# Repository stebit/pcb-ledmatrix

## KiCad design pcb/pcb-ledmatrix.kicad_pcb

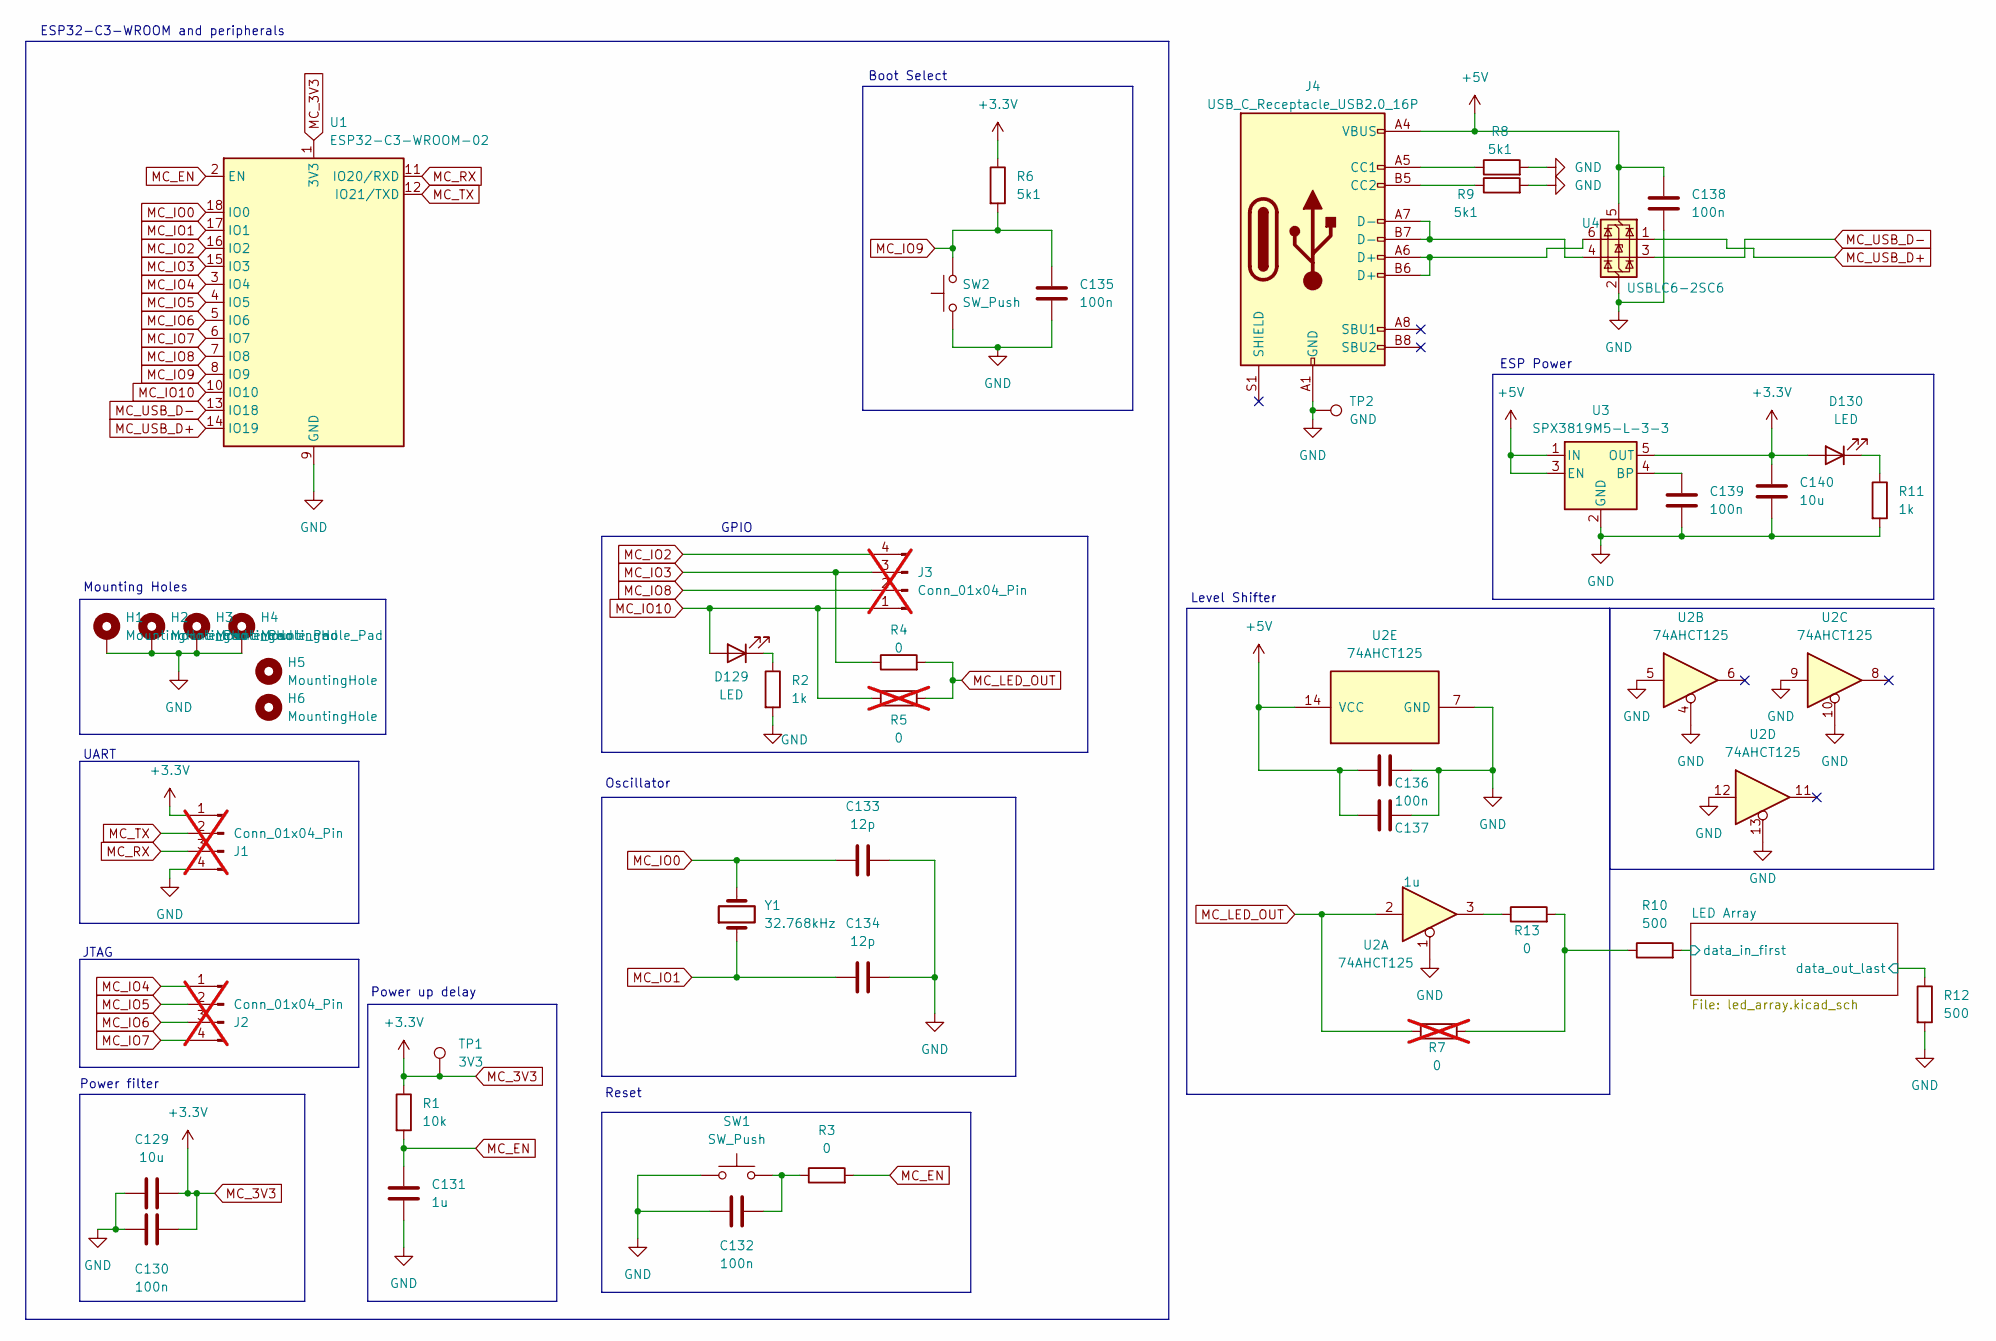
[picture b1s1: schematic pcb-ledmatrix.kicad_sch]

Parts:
C129, C140: 10u; C_0603_1608Metric
C130, C132, C135, C136, C138, C139: 100n; C_0603_1608Metric
C131, C137: 1u; C_0603_1608Metric
C133, C134: 12p; C_0603_1608Metric
D129, D130: LED; LED_0603_1608Metric; JLCPCB Part C2286
H1, H2, H3, H4: MountingHole_Pad; MountingHole_2.7mm_M2.5_DIN965_Pad
H5, H6: MountingHole; ToolingHole_1.152mm
J1, J2, J3: Conn_01x04_Pin; PinHeader_1x04_P2.54mm_Vertical; not fitted
J4: USB_C_Receptacle_USB2.0_16P; USB_C_Receptacle_HCTL_HC-TYPE-C-16P-01A; JLCPCB Part C393939
R1: 10k; R_0603_1608Metric
R2, R11: 1k; R_0603_1608Metric
R3, R4, R13: 0; R_0603_1608Metric
R5, R7: 0; R_0603_1608Metric; not fitted
R6, R8, R9: 5k1; R_0603_1608Metric
R10, R12: 500; R_0603_1608Metric
SW1, SW2: SW_Push; SW_Push_1P1T_XKB_TS-1187A; JLCPCB Part C318884
TP1: 3V3; TestPoint_Pad_2.0x2.0mm
TP2: GND; TestPoint_Pad_2.0x2.0mm
U1: ESP32-C3-WROOM-02; JLCPCB Part C2934560
U2: 74AHCT125; SOIC-14_3.9x8.7mm_P1.27mm; JLCPCB Part C155176
U3: SPX3819M5-L-3-3; SOT-23-5; JLCPCB Part C20617301
U4: USBLC6-2SC6; SOT-23-6
Y1: 32.768kHz; Crystal_SMD_3215-2Pin_3.2x1.5mm; JLCPCB Part C32346

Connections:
+5V: C136.1, C137.1, C138.1, J4.A4 (VBUS), J4.A9 (VBUS), J4.B4 (VBUS), J4.B9 (VBUS), U2.14 (VCC), U3.1 (IN), U3.3 (EN), U4.5 (VBUS); also elsewhere on the board
/LED Array/data_in_first: R10.2; also elsewhere on the board
/LED Array/data_out_last: R12.1; also elsewhere on the board
GND: C129.2, C130.1, C131.2, C132.1, C133.2, C134.2, C135.2, C136.2, C137.2, C138.2, C139.2, C140.2, H1.1, H2.1, H3.1, H4.1, J1.4, J4.A1 (GND), J4.A12 (GND), J4.B1 (GND), J4.B12 (GND), R2.2, R8.2, R9.2, R11.2, R12.2, SW1.1, SW2.1, TP2.1, U1.9 (GND), U1.19 (GND), U2.1, U2.4, U2.5, U2.7 (GND), U2.9, U2.10, U2.12, U2.13, U3.2 (GND), U4.2 (GND); also elsewhere on the board
MC_3V3: C129.1, C130.2, C140.1, D130.2 (A), J1.1, R1.1, R6.1, TP1.1, U1.1 (3V3), U3.5 (OUT)
MC_EN: C131.1, R1.2, R3.2, U1.2 (EN)
MC_IO0: C133.1, U1.18 (IO0), Y1.2
MC_IO1: C134.1, U1.17 (IO1), Y1.1
MC_IO2: J3.4, U1.16 (IO2)
MC_IO3: J3.3, R4.1, U1.15 (IO3)
MC_IO4: J2.1, U1.3 (IO4)
MC_IO5: J2.2, U1.4 (IO5)
MC_IO6: J2.3, U1.5 (IO6)
MC_IO7: J2.4, U1.6 (IO7)
MC_IO8: J3.2, U1.7 (IO8)
MC_IO9: C135.1, R6.2, SW2.2, U1.8 (IO9)
MC_IO10: D129.2 (A), J3.1, R5.1, U1.10 (IO10)
MC_LED_OUT: R4.2, R5.2, R7.1, U2.2
MC_RX: J1.3, U1.11 (IO20/RXD)
MC_TX: J1.2, U1.12 (IO21/TXD)
MC_USB_D+: U1.14 (IO19), U4.1 (I/O1)
MC_USB_D-: U1.13 (IO18), U4.3 (I/O2)
unnamed: C132.2, R3.1, SW1.2
unnamed: D129.1 (K), R2.1
unnamed: D130.1 (K), R11.1
unnamed: J4.A5 (CC1), R8.1
unnamed: J4.B5 (CC2), R9.1
unnamed: J4.A6 (D+), J4.B6 (D+), U4.6 (I/O1)
unnamed: J4.A7 (D-), J4.B7 (D-), U4.4 (I/O2)
unnamed: R7.2, R10.1, R13.2
unnamed: R13.1, U2.3
unnamed: C139.1, U3.4 (BP)

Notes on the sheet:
Power filter
UART
Power up delay
Level Shifter
Boot Select
JTAG
Oscillator
Reset
ESP32-C3-WROOM and peripherals
ESP Power
GPIO
Mounting Holes

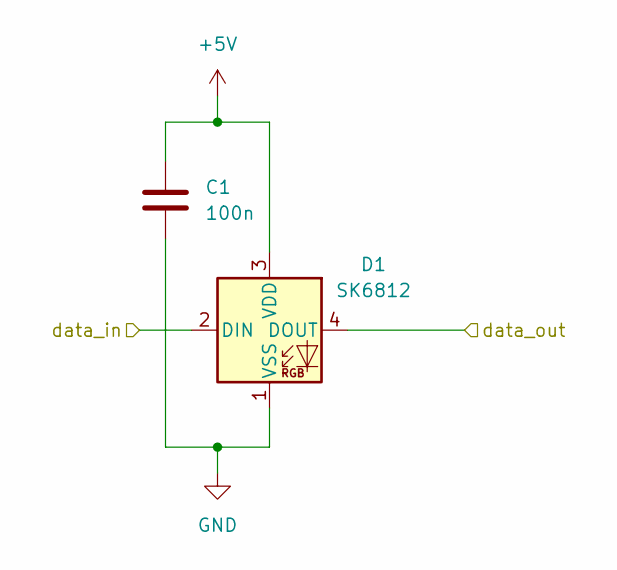
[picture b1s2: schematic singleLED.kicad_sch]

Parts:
C1: 100n; C_0603_1608Metric
D1: SK6812; LED_SK6812_PLCC4_5.0x5.0mm_P3.2mm

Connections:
+5V: C1.1, D1.3 (VDD); also elsewhere on the board
/LED Array/data_in_first: D1.2 (DIN); also elsewhere on the board
/LED Array/single LED/data_out: D1.4 (DOUT); also elsewhere on the board
GND: C1.2, D1.1 (VSS); also elsewhere on the board

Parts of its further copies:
C2, C3, C4, C5, C6, C7, C8, C9, C10, C11, C12, C13, C14, C15, C16, C17, C18, C19, C20, C21, C22, C23, C24, C25, C26, C27, C28, C29, C30, C31, C32, C33, C34, C35, C36, C37, C38, C39, C40, C41, C42, C43, C44, C45, C46, C47, C48, C49, C50, C51, C52, C53, C54, C55, C56, C57, C58, C59, C60, C61, C62, C63, C64, C65, C66, C67, C68, C69, C70, C71, C72, C73, C74, C75, C76, C77, C78, C79, C80, C81, C82, C83, C84, C85, C86, C87, C88, C89, C90, C91, C92, C93, C94, C95, C96, C97, C98, C99, C100, C101, C102, C103, C104, C105, C106, C107, C108, C109, C110, C111, C112, C113, C114, C115, C116, C117, C118, C119, C120, C121, C122, C123, C124, C125, C126, C127, C128: 100n; C_0603_1608Metric
D2, D3, D4, D5, D6, D7, D8, D9, D10, D11, D12, D13, D14, D15, D16, D17, D18, D19, D20, D21, D22, D23, D24, D25, D26, D27, D28, D29, D30, D31, D32, D33, D34, D35, D36, D37, D38, D39, D40, D41, D42, D43, D44, D45, D46, D47, D48, D49, D50, D51, D52, D53, D54, D55, D56, D57, D58, D59, D60, D61, D62, D63, D64, D65, D66, D67, D68, D69, D70, D71, D72, D73, D74, D75, D76, D77, D78, D79, D80, D81, D82, D83, D84, D85, D86, D87, D88, D89, D90, D91, D92, D93, D94, D95, D96, D97, D98, D99, D100, D101, D102, D103, D104, D105, D106, D107, D108, D109, D110, D111, D112, D113, D114, D115, D116, D117, D118, D119, D120, D121, D122, D123, D124, D125, D126, D127, D128: SK6812; LED_SK6812_PLCC4_5.0x5.0mm_P3.2mm

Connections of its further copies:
+5V: C2.1, C3.1, C4.1, C5.1, C6.1, C7.1, C8.1, C9.1, C10.1, C11.1, C12.1, C13.1, C14.1, C15.1, C16.1, C17.1, C18.1, C19.1, C20.1, C21.1, C22.1, C23.1, C24.1, C25.1, C26.1, C27.1, C28.1, C29.1, C30.1, C31.1, C32.1, C33.1, C34.1, C35.1, C36.1, C37.1, C38.1, C39.1, C40.1, C41.1, C42.1, C43.1, C44.1, C45.1, C46.1, C47.1, C48.1, C49.1, C50.1, C51.1, C52.1, C53.1, C54.1, C55.1, C56.1, C57.1, C58.1, C59.1, C60.1, C61.1, C62.1, C63.1, C64.1, C65.1, C66.1, C67.1, C68.1, C69.1, C70.1, C71.1, C72.1, C73.1, C74.1, C75.1, C76.1, C77.1, C78.1, C79.1, C80.1, C81.1, C82.1, C83.1, C84.1, C85.1, C86.1, C87.1, C88.1, C89.1, C90.1, C91.1, C92.1, C93.1, C94.1, C95.1, C96.1, C97.1, C98.1, C99.1, C100.1, C101.1, C102.1, C103.1, C104.1, C105.1, C106.1, C107.1, C108.1, C109.1, C110.1, C111.1, C112.1, C113.1, C114.1, C115.1, C116.1, C117.1, C118.1, C119.1, C120.1, C121.1, C122.1, C123.1, C124.1, C125.1, C126.1, C127.1, C128.1, D2.3 (VDD), D3.3 (VDD), D4.3 (VDD), D5.3 (VDD), D6.3 (VDD), D7.3 (VDD), D8.3 (VDD), D9.3 (VDD), D10.3 (VDD), D11.3 (VDD), D12.3 (VDD), D13.3 (VDD), D14.3 (VDD), D15.3 (VDD), D16.3 (VDD), D17.3 (VDD), D18.3 (VDD), D19.3 (VDD), D20.3 (VDD), D21.3 (VDD), D22.3 (VDD), D23.3 (VDD), D24.3 (VDD), D25.3 (VDD), D26.3 (VDD), D27.3 (VDD), D28.3 (VDD), D29.3 (VDD), D30.3 (VDD), D31.3 (VDD), D32.3 (VDD), D33.3 (VDD), D34.3 (VDD), D35.3 (VDD), D36.3 (VDD), D37.3 (VDD), D38.3 (VDD), D39.3 (VDD), D40.3 (VDD), D41.3 (VDD), D42.3 (VDD), D43.3 (VDD), D44.3 (VDD), D45.3 (VDD), D46.3 (VDD), D47.3 (VDD), D48.3 (VDD), D49.3 (VDD), D50.3 (VDD), D51.3 (VDD), D52.3 (VDD), D53.3 (VDD), D54.3 (VDD), D55.3 (VDD), D56.3 (VDD), D57.3 (VDD), D58.3 (VDD), D59.3 (VDD), D60.3 (VDD), D61.3 (VDD), D62.3 (VDD), D63.3 (VDD), D64.3 (VDD), D65.3 (VDD), D66.3 (VDD), D67.3 (VDD), D68.3 (VDD), D69.3 (VDD), D70.3 (VDD), D71.3 (VDD), D72.3 (VDD), D73.3 (VDD), D74.3 (VDD), D75.3 (VDD), D76.3 (VDD), D77.3 (VDD), D78.3 (VDD), D79.3 (VDD), D80.3 (VDD), D81.3 (VDD), D82.3 (VDD), D83.3 (VDD), D84.3 (VDD), D85.3 (VDD), D86.3 (VDD), D87.3 (VDD), D88.3 (VDD), D89.3 (VDD), D90.3 (VDD), D91.3 (VDD), D92.3 (VDD), D93.3 (VDD), D94.3 (VDD), D95.3 (VDD), D96.3 (VDD), D97.3 (VDD), D98.3 (VDD), D99.3 (VDD), D100.3 (VDD), D101.3 (VDD), D102.3 (VDD), D103.3 (VDD), D104.3 (VDD), D105.3 (VDD), D106.3 (VDD), D107.3 (VDD), D108.3 (VDD), D109.3 (VDD), D110.3 (VDD), D111.3 (VDD), D112.3 (VDD), D113.3 (VDD), D114.3 (VDD), D115.3 (VDD), D116.3 (VDD), D117.3 (VDD), D118.3 (VDD), D119.3 (VDD), D120.3 (VDD), D121.3 (VDD), D122.3 (VDD), D123.3 (VDD), D124.3 (VDD), D125.3 (VDD), D126.3 (VDD), D127.3 (VDD), D128.3 (VDD); also elsewhere on the board
/LED Array/data_out_last: D128.4 (DOUT); also elsewhere on the board
/LED Array/single LED1/data_out: D2.4 (DOUT), D3.2 (DIN)
/LED Array/single LED2/data_out: D3.4 (DOUT), D4.2 (DIN)
/LED Array/single LED3/data_out: D4.4 (DOUT), D5.2 (DIN)
/LED Array/single LED4/data_out: D5.4 (DOUT), D6.2 (DIN)
/LED Array/single LED5/data_out: D6.4 (DOUT), D7.2 (DIN)
/LED Array/single LED6/data_out: D7.4 (DOUT), D8.2 (DIN)
/LED Array/single LED7/data_out: D8.4 (DOUT), D9.2 (DIN)
/LED Array/single LED8/data_out: D9.4 (DOUT), D10.2 (DIN)
/LED Array/single LED10/data_in: D10.4 (DOUT), D11.2 (DIN)
/LED Array/single LED10/data_out: D11.4 (DOUT), D12.2 (DIN)
/LED Array/single LED11/data_out: D12.4 (DOUT), D13.2 (DIN)
/LED Array/single LED12/data_out: D13.4 (DOUT), D14.2 (DIN)
/LED Array/single LED13/data_out: D14.4 (DOUT), D15.2 (DIN)
/LED Array/single LED14/data_out: D15.4 (DOUT), D16.2 (DIN)
/LED Array/single LED15/data_out: D16.4 (DOUT), D17.2 (DIN)
/LED Array/single LED16/data_out: D17.4 (DOUT), D18.2 (DIN)
/LED Array/single LED17/data_out: D18.4 (DOUT), D19.2 (DIN)
/LED Array/single LED18/data_out: D19.4 (DOUT), D20.2 (DIN)
/LED Array/single LED19/data_out: D20.4 (DOUT), D21.2 (DIN)
/LED Array/single LED20/data_out: D21.4 (DOUT), D22.2 (DIN)
/LED Array/single LED21/data_out: D22.4 (DOUT), D23.2 (DIN)
/LED Array/single LED22/data_out: D23.4 (DOUT), D24.2 (DIN)
/LED Array/single LED23/data_out: D24.4 (DOUT), D25.2 (DIN)
/LED Array/single LED24/data_out: D25.4 (DOUT), D26.2 (DIN)
/LED Array/single LED25/data_out: D26.4 (DOUT), D27.2 (DIN)
/LED Array/single LED26/data_out: D27.4 (DOUT), D28.2 (DIN)
/LED Array/single LED27/data_out: D28.4 (DOUT), D29.2 (DIN)
/LED Array/single LED28/data_out: D29.4 (DOUT), D30.2 (DIN)
/LED Array/single LED29/data_out: D30.4 (DOUT), D31.2 (DIN)
/LED Array/single LED30/data_out: D31.4 (DOUT), D32.2 (DIN)
/LED Array/single LED31/data_out: D32.4 (DOUT), D33.2 (DIN)
/LED Array/single LED32/data_out: D33.4 (DOUT), D34.2 (DIN)
/LED Array/single LED33/data_out: D34.4 (DOUT), D35.2 (DIN)
/LED Array/single LED34/data_out: D35.4 (DOUT), D36.2 (DIN)
/LED Array/single LED35/data_out: D36.4 (DOUT), D37.2 (DIN)
/LED Array/single LED36/data_out: D37.4 (DOUT), D38.2 (DIN)
/LED Array/single LED37/data_out: D38.4 (DOUT), D39.2 (DIN)
/LED Array/single LED38/data_out: D39.4 (DOUT), D40.2 (DIN)
/LED Array/single LED39/data_out: D40.4 (DOUT), D41.2 (DIN)
/LED Array/single LED40/data_out: D41.4 (DOUT), D42.2 (DIN)
/LED Array/single LED41/data_out: D42.4 (DOUT), D43.2 (DIN)
/LED Array/single LED42/data_out: D43.4 (DOUT), D44.2 (DIN)
/LED Array/single LED43/data_out: D44.4 (DOUT), D45.2 (DIN)
/LED Array/single LED44/data_out: D45.4 (DOUT), D46.2 (DIN)
/LED Array/single LED45/data_out: D46.4 (DOUT), D47.2 (DIN)
/LED Array/single LED46/data_out: D47.4 (DOUT), D48.2 (DIN)
/LED Array/single LED47/data_out: D48.4 (DOUT), D49.2 (DIN)
/LED Array/single LED48/data_out: D49.4 (DOUT), D50.2 (DIN)
/LED Array/single LED49/data_out: D50.4 (DOUT), D51.2 (DIN)
/LED Array/single LED50/data_out: D51.4 (DOUT), D52.2 (DIN)
/LED Array/single LED51/data_out: D52.4 (DOUT), D53.2 (DIN)
/LED Array/single LED52/data_out: D53.4 (DOUT), D54.2 (DIN)
/LED Array/single LED53/data_out: D54.4 (DOUT), D55.2 (DIN)
/LED Array/single LED54/data_out: D55.4 (DOUT), D56.2 (DIN)
/LED Array/single LED55/data_out: D56.4 (DOUT), D57.2 (DIN)
/LED Array/single LED56/data_out: D57.4 (DOUT), D58.2 (DIN)
/LED Array/single LED57/data_out: D58.4 (DOUT), D59.2 (DIN)
/LED Array/single LED58/data_out: D59.4 (DOUT), D60.2 (DIN)
/LED Array/single LED59/data_out: D60.4 (DOUT), D61.2 (DIN)
/LED Array/single LED60/data_out: D61.4 (DOUT), D62.2 (DIN)
/LED Array/single LED61/data_out: D62.4 (DOUT), D63.2 (DIN)
/LED Array/single LED62/data_out: D63.4 (DOUT), D64.2 (DIN)
/LED Array/single LED63/data_out: D64.4 (DOUT), D65.2 (DIN)
/LED Array/single LED64/data_out: D65.4 (DOUT), D66.2 (DIN)
/LED Array/single LED65/data_out: D66.4 (DOUT), D67.2 (DIN)
/LED Array/single LED66/data_out: D67.4 (DOUT), D68.2 (DIN)
/LED Array/single LED67/data_out: D68.4 (DOUT), D69.2 (DIN)
/LED Array/single LED68/data_out: D69.4 (DOUT), D70.2 (DIN)
/LED Array/single LED69/data_out: D70.4 (DOUT), D71.2 (DIN)
/LED Array/single LED70/data_out: D71.4 (DOUT), D72.2 (DIN)
/LED Array/single LED71/data_out: D72.4 (DOUT), D73.2 (DIN)
/LED Array/single LED72/data_out: D73.4 (DOUT), D74.2 (DIN)
/LED Array/single LED73/data_out: D74.4 (DOUT), D75.2 (DIN)
/LED Array/single LED74/data_out: D75.4 (DOUT), D76.2 (DIN)
/LED Array/single LED75/data_out: D76.4 (DOUT), D77.2 (DIN)
/LED Array/single LED76/data_out: D77.4 (DOUT), D78.2 (DIN)
/LED Array/single LED77/data_out: D78.4 (DOUT), D79.2 (DIN)
/LED Array/single LED78/data_out: D79.4 (DOUT), D80.2 (DIN)
/LED Array/single LED79/data_out: D80.4 (DOUT), D81.2 (DIN)
/LED Array/single LED80/data_out: D81.4 (DOUT), D82.2 (DIN)
/LED Array/single LED81/data_out: D82.4 (DOUT), D83.2 (DIN)
/LED Array/single LED82/data_out: D83.4 (DOUT), D84.2 (DIN)
/LED Array/single LED83/data_out: D84.4 (DOUT), D85.2 (DIN)
/LED Array/single LED84/data_out: D85.4 (DOUT), D86.2 (DIN)
/LED Array/single LED85/data_out: D86.4 (DOUT), D87.2 (DIN)
/LED Array/single LED86/data_out: D87.4 (DOUT), D88.2 (DIN)
/LED Array/single LED87/data_out: D88.4 (DOUT), D89.2 (DIN)
/LED Array/single LED88/data_out: D89.4 (DOUT), D90.2 (DIN)
/LED Array/single LED89/data_out: D90.4 (DOUT), D91.2 (DIN)
/LED Array/single LED90/data_out: D91.4 (DOUT), D92.2 (DIN)
/LED Array/single LED91/data_out: D92.4 (DOUT), D93.2 (DIN)
/LED Array/single LED92/data_out: D93.4 (DOUT), D94.2 (DIN)
/LED Array/single LED93/data_out: D94.4 (DOUT), D95.2 (DIN)
/LED Array/single LED94/data_out: D95.4 (DOUT), D96.2 (DIN)
/LED Array/single LED95/data_out: D96.4 (DOUT), D97.2 (DIN)
/LED Array/single LED96/data_out: D97.4 (DOUT), D98.2 (DIN)
/LED Array/single LED97/data_out: D98.4 (DOUT), D99.2 (DIN)
/LED Array/single LED98/data_out: D99.4 (DOUT), D100.2 (DIN)
/LED Array/single LED100/data_in: D100.4 (DOUT), D101.2 (DIN)
/LED Array/single LED100/data_out: D101.4 (DOUT), D102.2 (DIN)
/LED Array/single LED101/data_out: D102.4 (DOUT), D103.2 (DIN)
/LED Array/single LED102/data_out: D103.4 (DOUT), D104.2 (DIN)
/LED Array/single LED103/data_out: D104.4 (DOUT), D105.2 (DIN)
/LED Array/single LED104/data_out: D105.4 (DOUT), D106.2 (DIN)
/LED Array/single LED105/data_out: D106.4 (DOUT), D107.2 (DIN)
/LED Array/single LED106/data_out: D107.4 (DOUT), D108.2 (DIN)
/LED Array/single LED107/data_out: D108.4 (DOUT), D109.2 (DIN)
/LED Array/single LED108/data_out: D109.4 (DOUT), D110.2 (DIN)
/LED Array/single LED109/data_out: D110.4 (DOUT), D111.2 (DIN)
/LED Array/single LED110/data_out: D111.4 (DOUT), D112.2 (DIN)
/LED Array/single LED111/data_out: D112.4 (DOUT), D113.2 (DIN)
/LED Array/single LED112/data_out: D113.4 (DOUT), D114.2 (DIN)
/LED Array/single LED113/data_out: D114.4 (DOUT), D115.2 (DIN)
/LED Array/single LED114/data_out: D115.4 (DOUT), D116.2 (DIN)
/LED Array/single LED115/data_out: D116.4 (DOUT), D117.2 (DIN)
/LED Array/single LED116/data_out: D117.4 (DOUT), D118.2 (DIN)
/LED Array/single LED117/data_out: D118.4 (DOUT), D119.2 (DIN)
/LED Array/single LED118/data_out: D119.4 (DOUT), D120.2 (DIN)
/LED Array/single LED119/data_out: D120.4 (DOUT), D121.2 (DIN)
/LED Array/single LED120/data_out: D121.4 (DOUT), D122.2 (DIN)
/LED Array/single LED121/data_out: D122.4 (DOUT), D123.2 (DIN)
/LED Array/single LED122/data_out: D123.4 (DOUT), D124.2 (DIN)
/LED Array/single LED123/data_out: D124.4 (DOUT), D125.2 (DIN)
/LED Array/single LED124/data_out: D125.4 (DOUT), D126.2 (DIN)
/LED Array/single LED125/data_out: D126.4 (DOUT), D127.2 (DIN)
/LED Array/single LED126/data_out: D127.4 (DOUT), D128.2 (DIN)
/LED Array/single LED/data_out: D2.2 (DIN); also elsewhere on the board
GND: C2.2, C3.2, C4.2, C5.2, C6.2, C7.2, C8.2, C9.2, C10.2, C11.2, C12.2, C13.2, C14.2, C15.2, C16.2, C17.2, C18.2, C19.2, C20.2, C21.2, C22.2, C23.2, C24.2, C25.2, C26.2, C27.2, C28.2, C29.2, C30.2, C31.2, C32.2, C33.2, C34.2, C35.2, C36.2, C37.2, C38.2, C39.2, C40.2, C41.2, C42.2, C43.2, C44.2, C45.2, C46.2, C47.2, C48.2, C49.2, C50.2, C51.2, C52.2, C53.2, C54.2, C55.2, C56.2, C57.2, C58.2, C59.2, C60.2, C61.2, C62.2, C63.2, C64.2, C65.2, C66.2, C67.2, C68.2, C69.2, C70.2, C71.2, C72.2, C73.2, C74.2, C75.2, C76.2, C77.2, C78.2, C79.2, C80.2, C81.2, C82.2, C83.2, C84.2, C85.2, C86.2, C87.2, C88.2, C89.2, C90.2, C91.2, C92.2, C93.2, C94.2, C95.2, C96.2, C97.2, C98.2, C99.2, C100.2, C101.2, C102.2, C103.2, C104.2, C105.2, C106.2, C107.2, C108.2, C109.2, C110.2, C111.2, C112.2, C113.2, C114.2, C115.2, C116.2, C117.2, C118.2, C119.2, C120.2, C121.2, C122.2, C123.2, C124.2, C125.2, C126.2, C127.2, C128.2, D2.1 (VSS), D3.1 (VSS), D4.1 (VSS), D5.1 (VSS), D6.1 (VSS), D7.1 (VSS), D8.1 (VSS), D9.1 (VSS), D10.1 (VSS), D11.1 (VSS), D12.1 (VSS), D13.1 (VSS), D14.1 (VSS), D15.1 (VSS), D16.1 (VSS), D17.1 (VSS), D18.1 (VSS), D19.1 (VSS), D20.1 (VSS), D21.1 (VSS), D22.1 (VSS), D23.1 (VSS), D24.1 (VSS), D25.1 (VSS), D26.1 (VSS), D27.1 (VSS), D28.1 (VSS), D29.1 (VSS), D30.1 (VSS), D31.1 (VSS), D32.1 (VSS), D33.1 (VSS), D34.1 (VSS), D35.1 (VSS), D36.1 (VSS), D37.1 (VSS), D38.1 (VSS), D39.1 (VSS), D40.1 (VSS), D41.1 (VSS), D42.1 (VSS), D43.1 (VSS), D44.1 (VSS), D45.1 (VSS), D46.1 (VSS), D47.1 (VSS), D48.1 (VSS), D49.1 (VSS), D50.1 (VSS), D51.1 (VSS), D52.1 (VSS), D53.1 (VSS), D54.1 (VSS), D55.1 (VSS), D56.1 (VSS), D57.1 (VSS), D58.1 (VSS), D59.1 (VSS), D60.1 (VSS), D61.1 (VSS), D62.1 (VSS), D63.1 (VSS), D64.1 (VSS), D65.1 (VSS), D66.1 (VSS), D67.1 (VSS), D68.1 (VSS), D69.1 (VSS), D70.1 (VSS), D71.1 (VSS), D72.1 (VSS), D73.1 (VSS), D74.1 (VSS), D75.1 (VSS), D76.1 (VSS), D77.1 (VSS), D78.1 (VSS), D79.1 (VSS), D80.1 (VSS), D81.1 (VSS), D82.1 (VSS), D83.1 (VSS), D84.1 (VSS), D85.1 (VSS), D86.1 (VSS), D87.1 (VSS), D88.1 (VSS), D89.1 (VSS), D90.1 (VSS), D91.1 (VSS), D92.1 (VSS), D93.1 (VSS), D94.1 (VSS), D95.1 (VSS), D96.1 (VSS), D97.1 (VSS), D98.1 (VSS), D99.1 (VSS), D100.1 (VSS), D101.1 (VSS), D102.1 (VSS), D103.1 (VSS), D104.1 (VSS), D105.1 (VSS), D106.1 (VSS), D107.1 (VSS), D108.1 (VSS), D109.1 (VSS), D110.1 (VSS), D111.1 (VSS), D112.1 (VSS), D113.1 (VSS), D114.1 (VSS), D115.1 (VSS), D116.1 (VSS), D117.1 (VSS), D118.1 (VSS), D119.1 (VSS), D120.1 (VSS), D121.1 (VSS), D122.1 (VSS), D123.1 (VSS), D124.1 (VSS), D125.1 (VSS), D126.1 (VSS), D127.1 (VSS), D128.1 (VSS); also elsewhere on the board

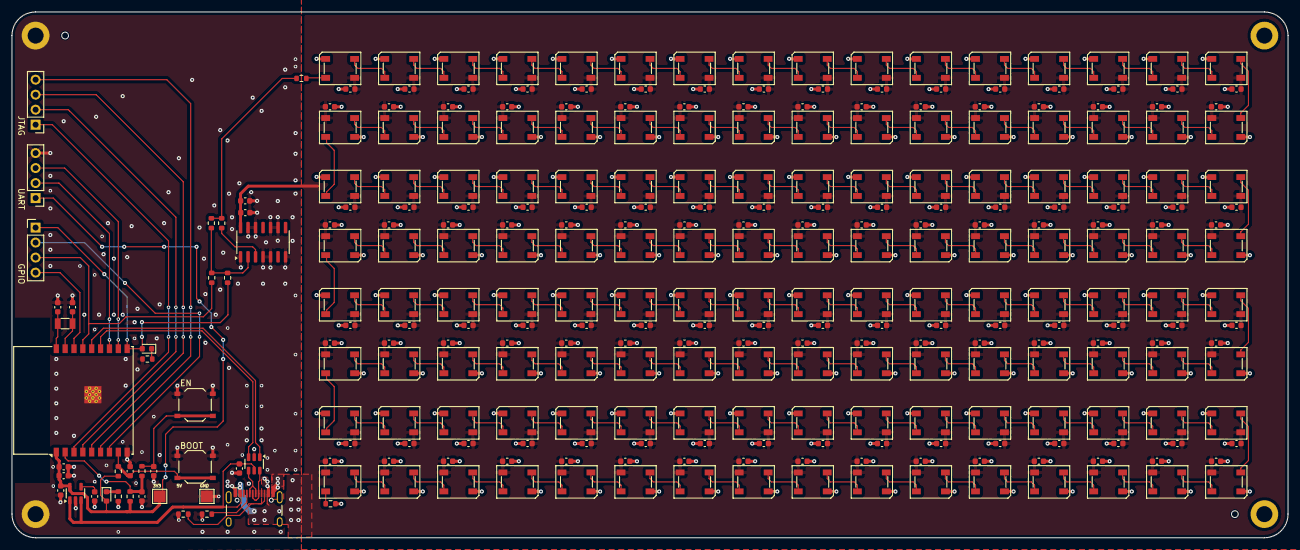
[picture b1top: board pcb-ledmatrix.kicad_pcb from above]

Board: 2 copper layers, 216.0 x 89.0 mm, 302 parts (0 on the bottom side), 159 nets.

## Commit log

2025-06-03 add kicad project
2025-06-05 change level shifter in schematic
2025-06-05 finisch layout, add prod files
2025-07-01 add gitignore for esphome
2025-07-01 add esphome config
